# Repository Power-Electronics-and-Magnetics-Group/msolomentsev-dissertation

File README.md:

# msolomentsev-dissertation
Supplementary materials and files from Michael Solomentsev's dissertation.

Contents:
- Experimental data from all experiments described in the dissertation.
- MATLAB scripts implementing the current distribution method described in Chapter 3.
- PCB design files for converters and test boards.
- Microcontroller code implementing maximum power point tracking for the differential power processing work in Chapter 5.

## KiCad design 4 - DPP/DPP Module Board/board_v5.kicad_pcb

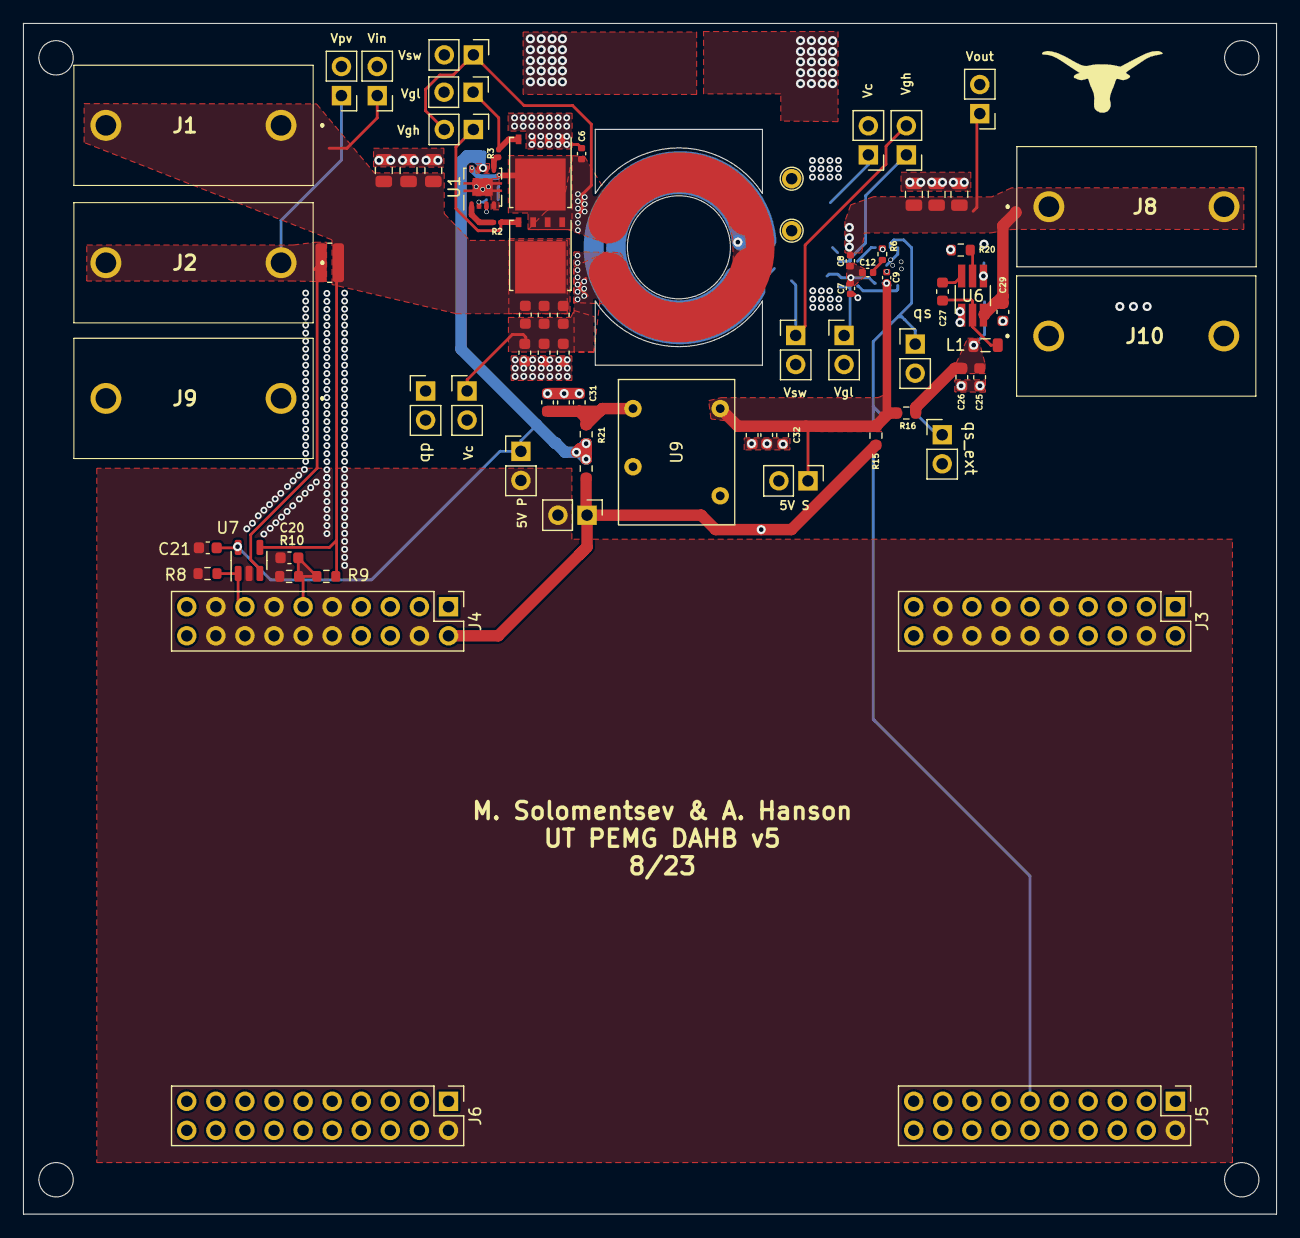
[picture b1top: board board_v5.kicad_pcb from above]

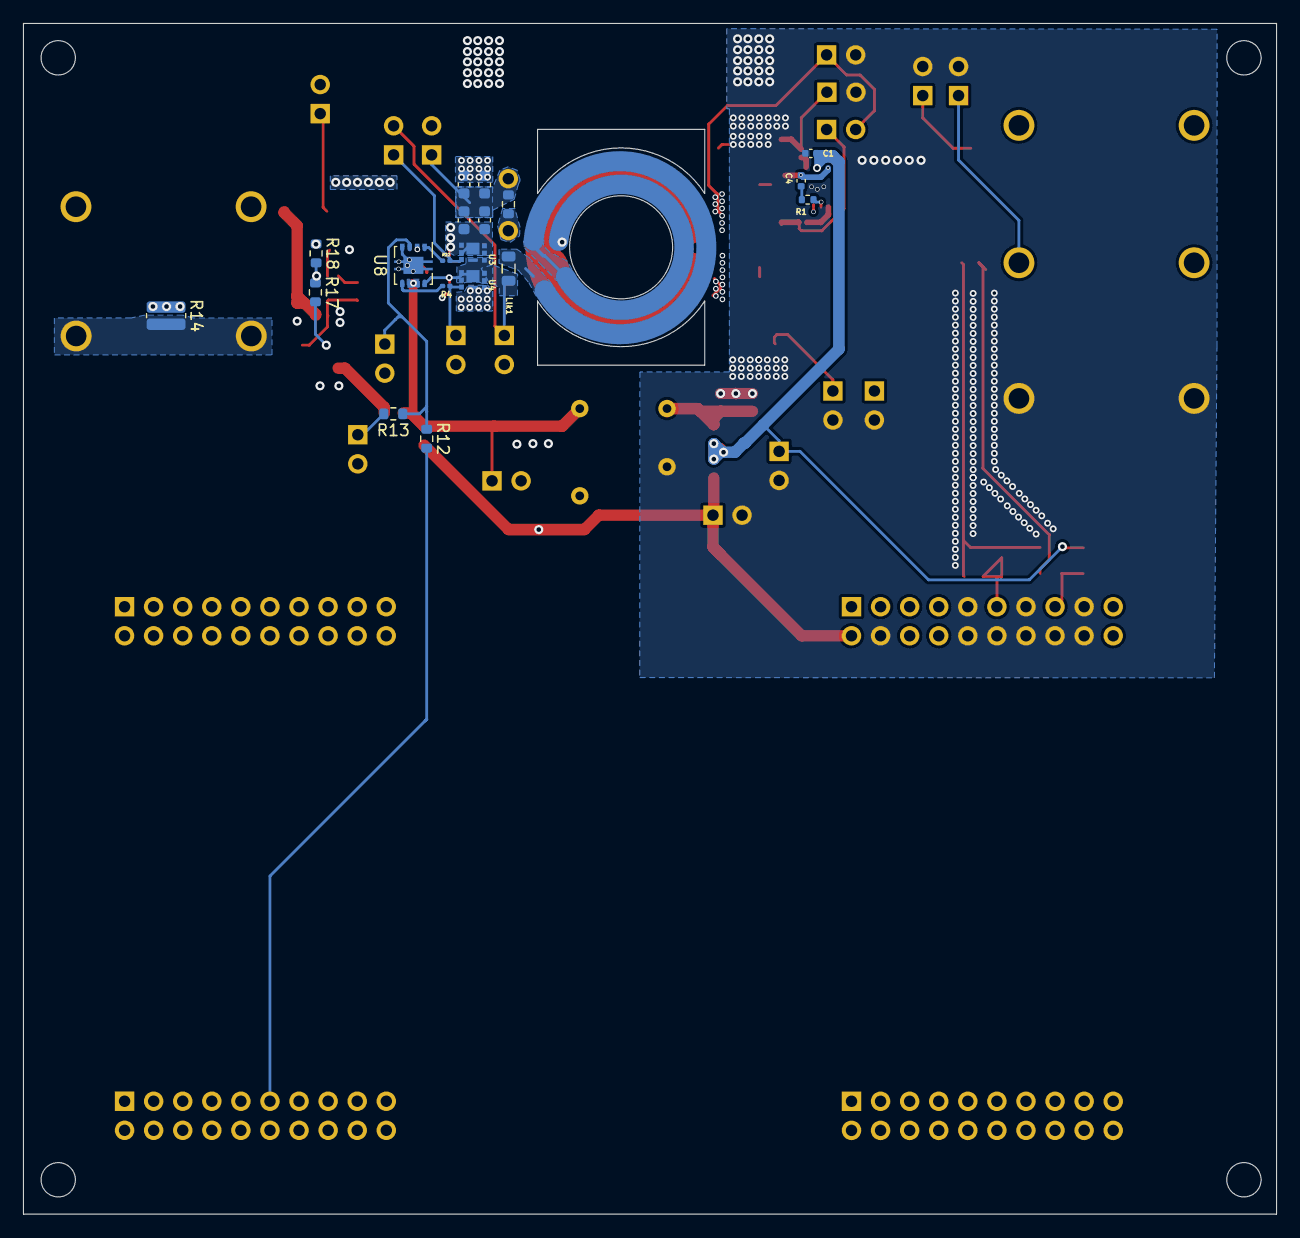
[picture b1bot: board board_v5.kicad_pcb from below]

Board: 4 copper layers, 109.5 x 104.0 mm, 89 parts (19 on the bottom side), 37 nets.

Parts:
5V P, 5V S: TP_Header; PinHeader_1x02_P2.54mm_Vertical
C1, C9: 1u; C_0402_1005Metric
C2, C2#2, C3, C13, C14, C14#2, C31: 10u; C_0603_1608Metric
C4: 100n; C_0402_1005Metric
C6, C7, C8: C; C_0402_1005Metric
C10, C11, C15, C16: 330n; C_0603_1608Metric
C12: 18n; C_0402_1005Metric
C17, C18, C19: 47u; C_0805_2012Metric
C20, C21, C29: 1u; C_0603_1608Metric
C22, C23, C24: 4.7u; C_0805_2012Metric
C25, C26: 22u; C_0603_1608Metric
C27: 100n; L_0603_1608Metric
C32: 4.7u; C_0603_1608Metric
J1, J2, J8, J9, J10: Conn_01x01_Female; deltronconnector
J3, J4, J5, J6: Conn_02x10_Row_Letter_First; PinHeader_2x10_P2.54mm_Vertical_LetterNumber
J7: Conn_01x02_Female; PinHeader_1x02_P2.54mm_Vertical
L1: 4.7n; L_0805_2012Metric
Llk1: 240n; L_0805_2012Metric
R1, R6: 0; R_0402_1005Metric
R2, R3, R4, R22: 0; R_0201_0603Metric
R5, R7, R12, R13, R15, R16, R21: 0; R_0603_1608Metric
R8: R; R_0603_1608Metric
R9, R10, R18: 10k; R_0603_1608Metric
R14: 0; R_0612_1632Metric
R17: 56k; R_0603_1608Metric
R20: 100M; R_0603_1608Metric
R_Isense1: 50u; R_0612_1632Metric
TP10: TP_Header; PinHeader_1x02_P2.54mm_Vertical
U1, U8: TPS28225; Texas_S-PVSON-N8_modified
U2, U5: OptiMOS; TDSON-8-1
U3, U4: RF4E070GNTR; 8-PowerUDFN
U6: AP62200_TSOT; TSOT-23-6_HandSoldering
U7: INA180/139; SOT-23-5
U9: iso_dcdc; mornstar_dcdc
Vc: TP_Header; PinHeader_1x02_P2.54mm_Vertical
Vc#2: TP_Header; PinHeader_1x02_P2.54mm_Vertical
Vgh: TP_Header; PinHeader_1x02_P2.54mm_Vertical
Vgh#2: TP_Header; PinHeader_1x02_P2.54mm_Vertical
Vgl: TP_Header; PinHeader_1x02_P2.54mm_Vertical
Vgl#2: TP_Header; PinHeader_1x02_P2.54mm_Vertical
Vin: TP_Header; PinHeader_1x02_P2.54mm_Vertical
Vout: TP_Header; PinHeader_1x02_P2.54mm_Vertical
Vpv: TP_Header; PinHeader_1x02_P2.54mm_Vertical
Vsw: TP_Header; PinHeader_1x02_P2.54mm_Vertical
Vsw#2: TP_Header; PinHeader_1x02_P2.54mm_Vertical
qp: TP_Header; PinHeader_1x02_P2.54mm_Vertical
qs: TP_Header; PinHeader_1x02_P2.54mm_Vertical

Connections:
+5V: J3.b1, J4.b1, J7.1, R5.2, R15.2
/5V_primary: 5V P.1, C1.1, C21.1, R5.1, R21.1, U1.6 (VDD), U1.7 (EN/PG), U7.5 (V+)
/5v_buck: C25.1, C26.1, L1.1, R16.2, R17.2
/5v_iso: C31.1, R21.2, U9.3 (Vout)
/5v_sec: 5V S.1, C9.1, C32.1, R15.1, R16.1, U8.6 (VDD), U8.7 (EN/PG), U9.2 (Vin)
/V_i_sense: J4.a8, R8.1, U7.1
/V_in_low: C20.1, J4.a6, R9.1, R10.2
/i_in+: J2.1, R_Isense1.1, U7.3 (+), Vpv.1
/p_g_h: R2.2, U2.4 (G), Vgh#2.1
/p_g_l: R3.1, U5.4 (G), Vgl.1
/q_p: J4.a3, U1.3 (PWM), qp.1
/q_s_iso: R13.2, TP10.1
/q_s_mcu: J5.a6, R12.2
/s_g_h: R22.2, U3.3 (G), Vgh.1
/s_g_l: R4.1, U4.3 (G), Vgl#2.1
/x_s: C7.2, C8.2, C12.2, Llk1.1, U3.4 (S), U3.8 (S), U4.1 (D), U4.2 (D), U4.5 (D), U4.6 (D), U4.7 (D), U8.8 (PHASE), Vgh.2, Vsw#2.1
GND: 5V P.2, C1.2, C3.2, C6.1, C14.2, C14#2.2, C17.2, C18.2, C19.2, C20.2, C21.2, C31.2, J3.a5, J3.a7, J3.a9, J3.b2, J3.b5, J3.b6, J3.b7, J3.b8, J3.b9, J4.a5, J4.a7, J4.a9, J4.b2, J4.b5, J4.b6, J4.b7, J4.b8, J4.b9, J5.b1, J6.b1, J7.2, J9.1, R8.2, R10.1, U1.4 (GND), U1.9 (PAD), U5.1 (S), U5.2 (S), U5.3 (S), U7.2 (GND), U9.4 (GND), Vc.2, Vgl.2, Vin.2, Vpv.2, Vsw.2, qp.2
GND1: 5V S.2, C7.1, C9.2, C11.2, C16.2, C22.2, C23.2, C24.2, C25.2, C26.2, C29.2, C32.2, R14.1, R18.1, R20.1, TP10.2, U4.4 (S), U4.8 (S), U6.1 (GND), U8.4 (GND), U8.9 (PAD), U9.1 (0V), Vc#2.2, Vgl#2.2, Vout.2, Vsw#2.2, qs.2
unnamed: C4.1, R1.2
unnamed: C10.2, C11.1, C15.2, C16.1, R7.2, Vc#2.1
unnamed: C12.1, R6.2
unnamed: C27.1, L1.2, U6.2 (SW)
unnamed: C27.2, U6.6 (BST)
unnamed: J10.1, R14.2
unnamed: R1.1, U1.2 (BOOT)
unnamed: R6.1, U8.2 (BOOT)
unnamed: R12.1, R13.1, U8.3 (PWM)
unnamed: R17.1, R18.2, U6.4 (FB)
unnamed: R20.2, U6.5 (EN)
P_G_H: R2.1, U1.1 (UGATE)
P_G_L: R3.2, U1.5 (LGATE)
P_SW: C2.2, C2#2.2, C3.1, C4.2, C6.2, C13.2, C14.1, C14#2.1, U1.8 (PHASE), U2.1 (S), U2.2 (S), U2.3 (S), U5.5 (D), Vc.1, Vgh#2.2, Vsw.1
S_G_H: R22.1, U8.1 (UGATE)
S_G_L: R4.2, U8.5 (LGATE)
S_SW: Llk1.2, R7.1
V_IN: C2.1, C2#2.1, C13.1, C17.1, C18.1, C19.1, J1.1, R9.2, R_Isense1.2, U2.5 (D), U7.4 (-), Vin.1
V_OUT: C8.1, C10.1, C15.1, C22.1, C23.1, C24.1, C29.1, J8.1, U3.1 (D), U3.2 (D), U3.5 (D), U3.6 (D), U3.7 (D), U6.3 (Vin), Vout.1

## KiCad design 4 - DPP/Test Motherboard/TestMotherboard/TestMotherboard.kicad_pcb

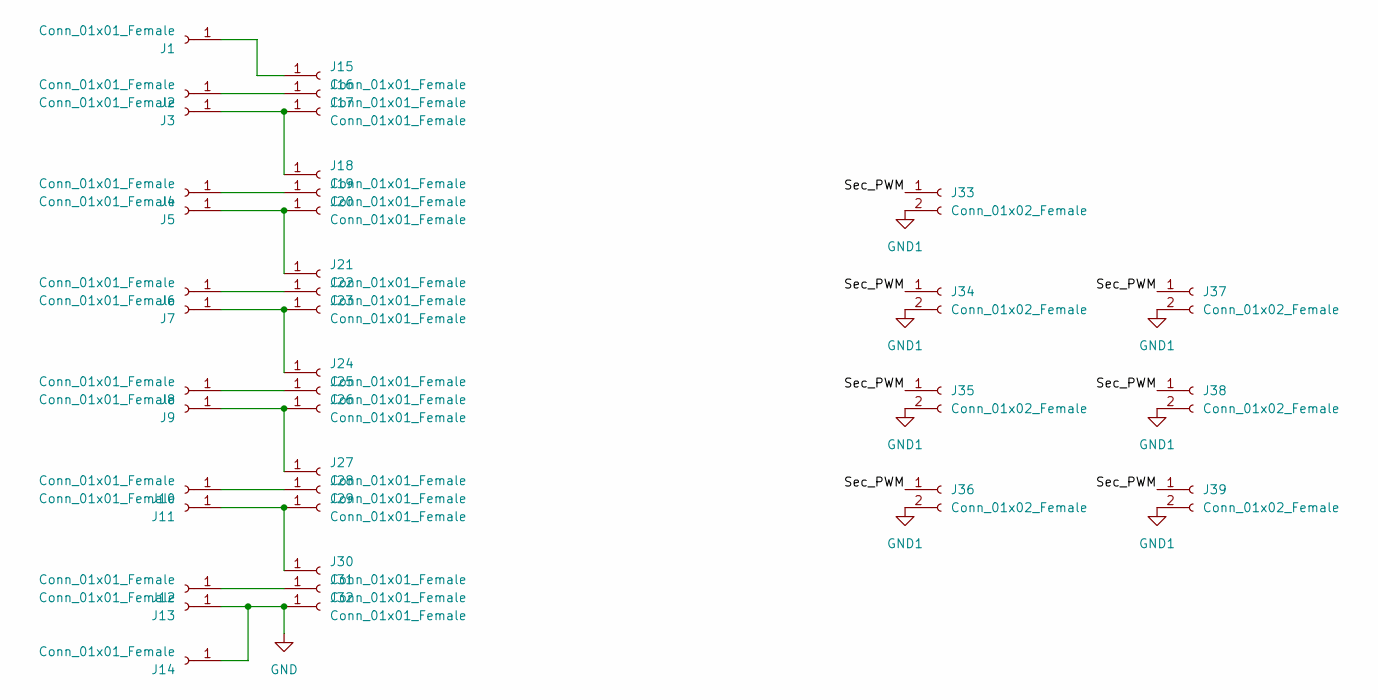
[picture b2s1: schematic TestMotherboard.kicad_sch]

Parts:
J1, J2, J3, J4, J5, J6, J7, J8, J9, J10, J11, J12, J13, J14: Conn_01x01_Female; deltronconnector
J15, J16, J17, J18, J19, J20, J21, J22, J23, J24, J25, J26, J27, J28, J29, J30, J31, J32: Conn_01x01_Female; VerticalBananaPlug
J33, J34, J35, J36, J37, J38, J39: Conn_01x02_Female; PinHeader_1x02_P2.54mm_Vertical

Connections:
/Sec_PWM: J33.1, J34.1, J35.1, J36.1, J37.1, J38.1, J39.1; also elsewhere on the board
GND: J13.1, J14.1, J32.1
GND1: J33.2, J34.2, J35.2, J36.2, J37.2, J38.2, J39.2; also elsewhere on the board
unnamed: J1.1, J15.1
unnamed: J10.1, J28.1
unnamed: J11.1, J29.1, J30.1
unnamed: J12.1, J31.1
unnamed: J2.1, J16.1
unnamed: J3.1, J17.1, J18.1
unnamed: J4.1, J19.1
unnamed: J5.1, J20.1, J21.1
unnamed: J6.1, J22.1
unnamed: J7.1, J23.1, J24.1
unnamed: J8.1, J25.1
unnamed: J9.1, J26.1, J27.1

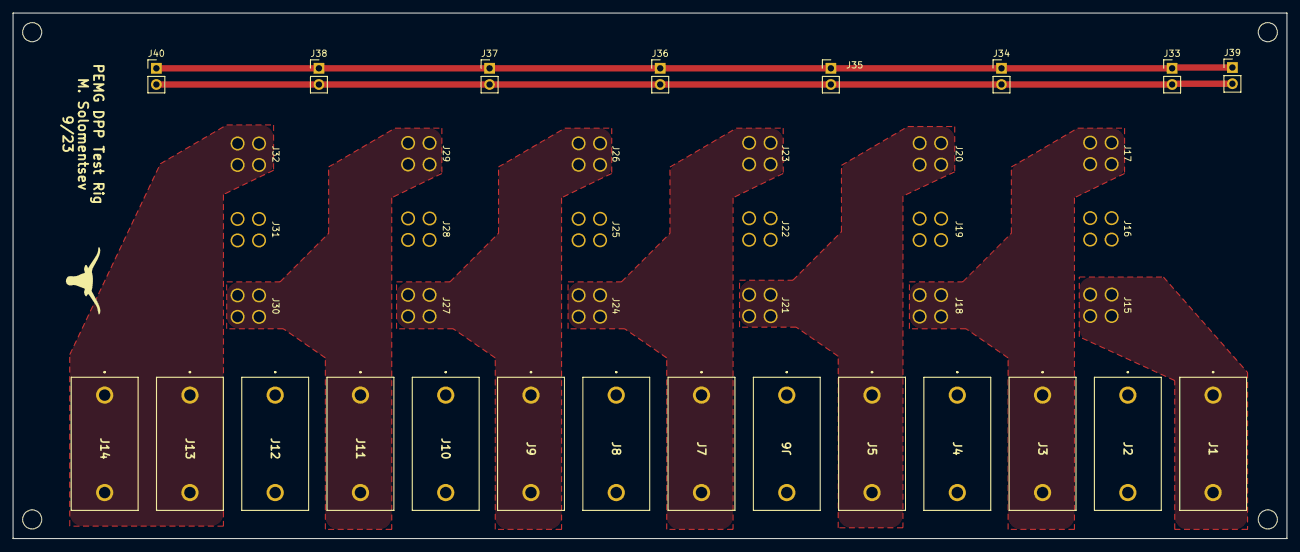
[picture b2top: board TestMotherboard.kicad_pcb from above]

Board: 2 copper layers, 200.0 x 82.5 mm, 40 parts (0 on the bottom side), 15 nets.

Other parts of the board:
J40: Conn_01x02_Female; PinHeader_1x02_P2.54mm_Vertical

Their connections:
/Sec_PWM: J40.1; also elsewhere on the board
GND1: J40.2; also elsewhere on the board

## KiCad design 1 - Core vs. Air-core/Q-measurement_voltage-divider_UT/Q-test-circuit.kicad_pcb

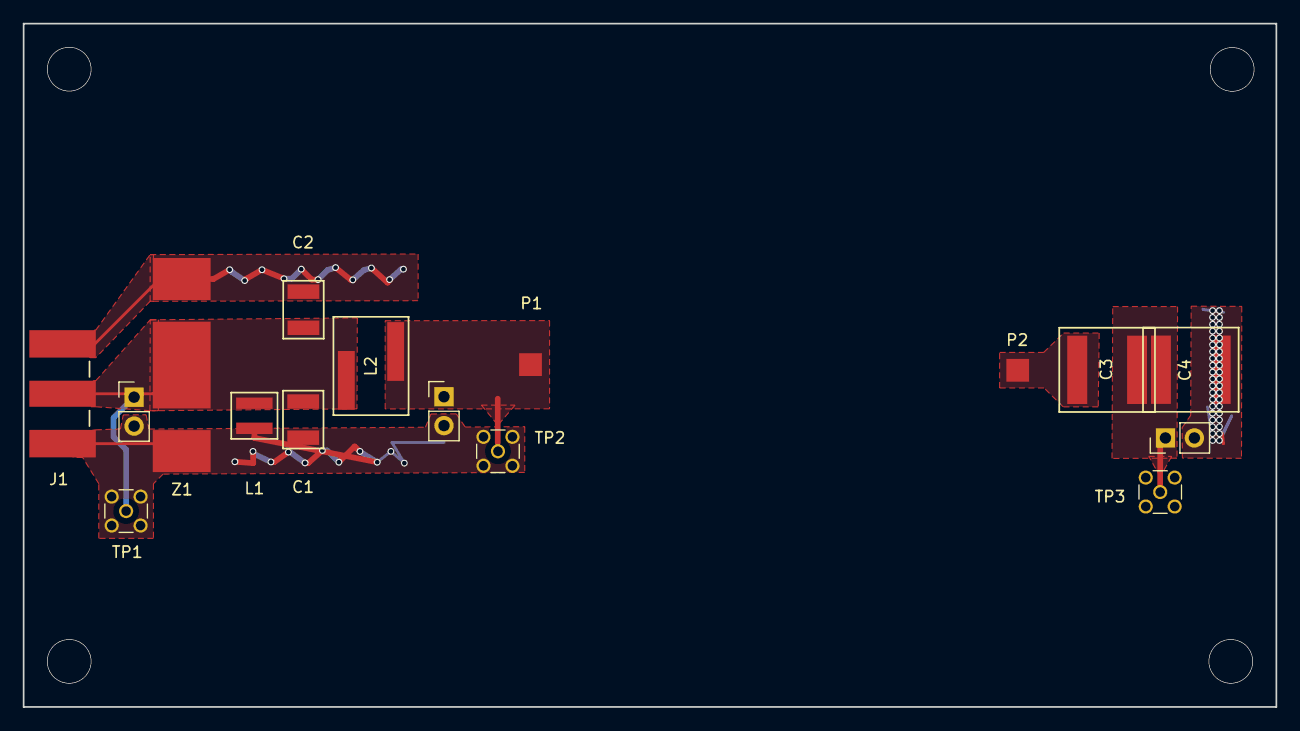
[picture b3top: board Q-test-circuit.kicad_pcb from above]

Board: 2 copper layers, 110.0 x 60.0 mm, 16 parts (0 on the bottom side), 5 nets.

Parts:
C1, C2: C; atc_100b
C3, C4: C; 2220
J1: CONN_73251-1150_MOL; SMA-noSilkscreen
L1: L; wurth_fixedind160nH
L2: L; wurth_fixedind60nH
P1, P2: terminal; pin_smd
TP1, TP2, TP3: PinHeader_1x02_P2.54mm_Vertical
TP1#2, TP2#2, TP3#2: MMCX_Molex_73415-1471_Vertical
Z1: z-transformer; avx-m4

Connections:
/vout: C3.2, C4.1, TP3.1, TP3#2.1
GND: C1.2, C2.2, C4.2, J1.2, J1.3, L1.2, TP1.2, TP1#2.2, TP2.2, TP2#2.2, TP3.2, TP3#2.2, Z1.1, Z1.3
unnamed: C1.1, C2.1, J1.1, L1.1, L2.2, TP1.1, TP1#2.1, Z1.2
unnamed: C3.1, P2.1
unnamed: L2.1, P1.1, TP2.1, TP2#2.1

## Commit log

2023-10-10 added materials

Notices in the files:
parts and their libraries:
Copyright 2016 Accelerated Designs. All rights reserved.
